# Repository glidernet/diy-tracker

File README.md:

# diy-tracker
Do-it-Yourself OGN Tracker software

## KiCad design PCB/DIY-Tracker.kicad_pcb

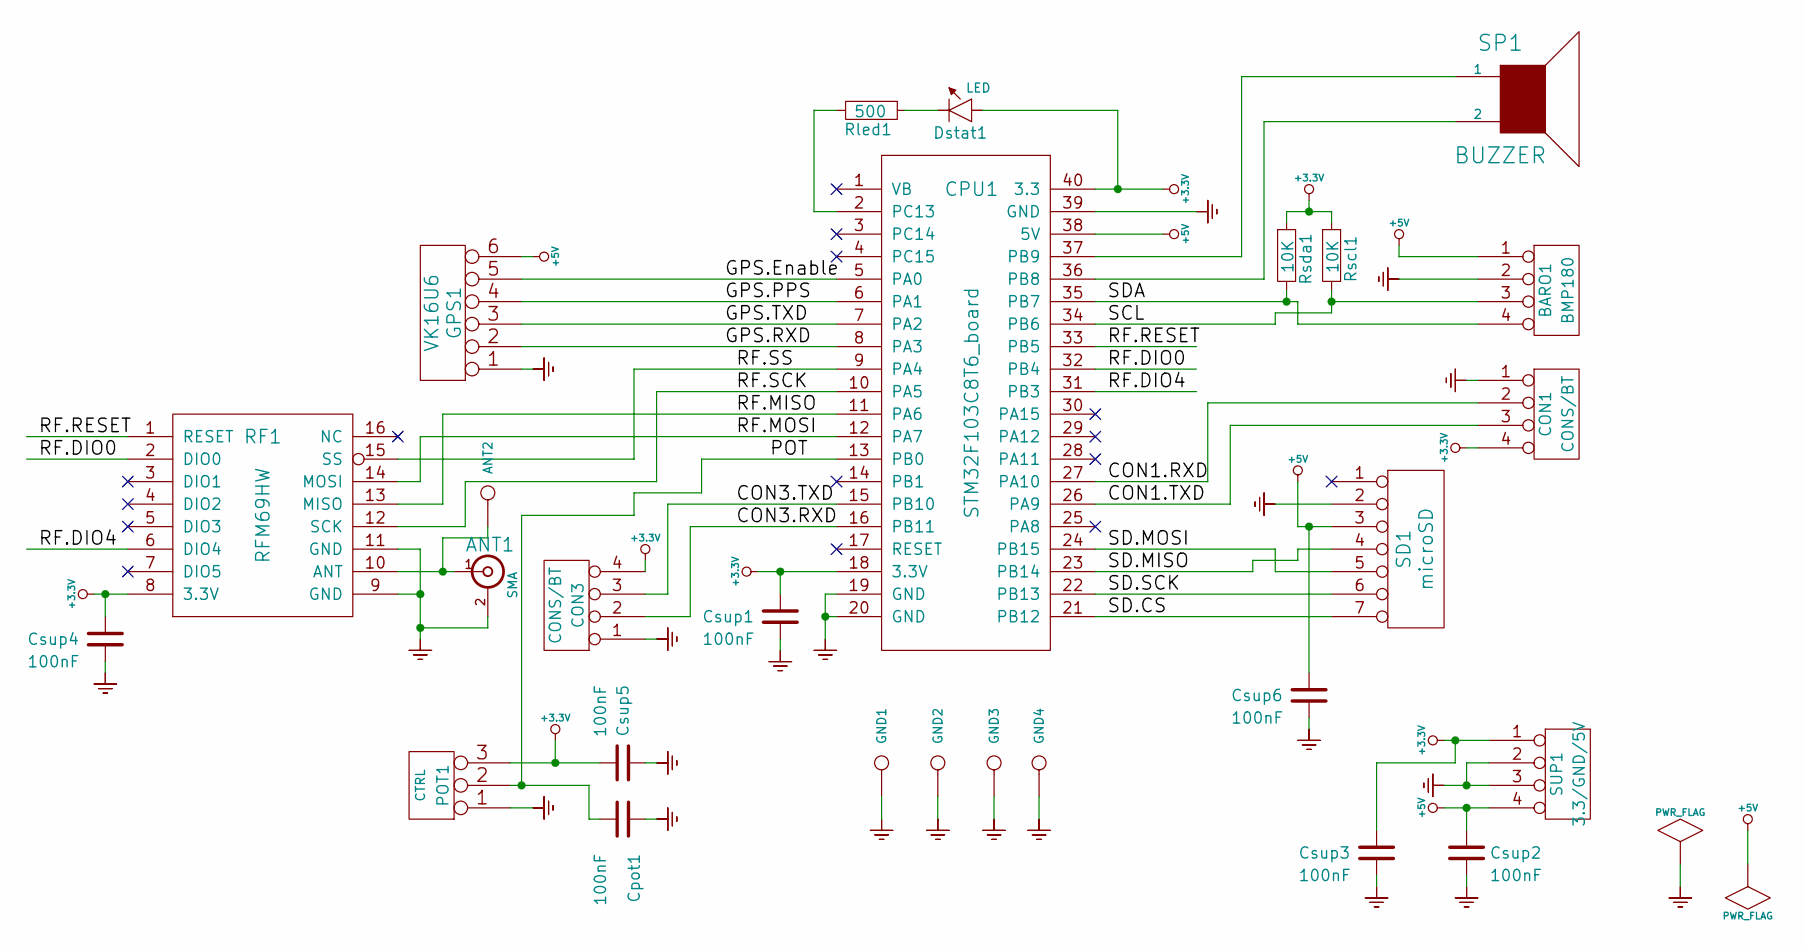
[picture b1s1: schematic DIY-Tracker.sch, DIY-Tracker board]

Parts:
ANT1: SMA; SIL-2
ANT2: CONN_1; 1pin
BARO1: BMP180; SIL-4
CON1, CON3: CONS/BT; SIL-4
CPU1: STM32F103C8T6_board; DIP-40__600_ELL
Cpot1: 100nF; c_1206
Csup1, Csup2, Csup3, Csup4, Csup5, Csup6: 100nF; c_1206
Dstat1: LED; SIL-2
GND1, GND2, GND3, GND4: CONN_1; 1pin
GPS1: VK16U6; SIL-6
POT1: CTRL; SIL-3
RF1: RFM69HW
Rled1: 500; c_1206
Rscl1: 10K; c_1206
Rsda1: 10K; c_1206
SD1: microSD; SIL-7
SP1: BUZZER; SIL-2
SUP1: 3.3/GND/5V; SIL-4

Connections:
+3.3V: CON1.4, CON3.4, CPU1.18 (3.3V), CPU1.40 (3.3), Csup1.1, Csup3.1, Csup4.1, Csup5.2, Dstat1.1 (A), POT1.3, RF1.8 (3.3V), Rscl1.1, Rsda1.1, SUP1.1
+5V: BARO1.1, CPU1.38 (5V), Csup2.1, Csup6.1, GPS1.6, SD1.3, SUP1.4
/CON1.RXD: CON1.2, CPU1.27 (PA10)
/CON1.TXD: CON1.3, CPU1.26 (PA9)
/CON3.RXD: CON3.2, CPU1.16 (PB11)
/CON3.TXD: CON3.3, CPU1.15 (PB10)
/GPS.Enable: CPU1.5 (PA0), GPS1.5
/GPS.PPS: CPU1.6 (PA1), GPS1.4
/GPS.RXD: CPU1.8 (PA3), GPS1.2
/GPS.TXD: CPU1.7 (PA2), GPS1.3
/POT: CPU1.13 (PB0), Cpot1.2, POT1.2 (PM)
/RF.DIO0: CPU1.32 (PB4), RF1.2 (DIO0)
/RF.DIO4: CPU1.31 (PB3), RF1.6 (DIO4)
/RF.MISO: CPU1.11 (PA6), RF1.13 (MISO)
/RF.MOSI: CPU1.12 (PA7), RF1.14 (MOSI)
/RF.RESET: CPU1.33 (PB5), RF1.1 (RESET)
/RF.SCK: CPU1.10 (PA5), RF1.12 (SCK)
/RF.SS: CPU1.9 (PA4), RF1.15 (SS)
/SCL: BARO1.3, CPU1.34 (PB6), Rscl1.2
/SD.CS: CPU1.21 (PB12), SD1.7
/SD.MISO: CPU1.23 (PB14), SD1.4
/SD.MOSI: CPU1.24 (PB15), SD1.5
/SD.SCK: CPU1.22 (PB13), SD1.6
/SDA: BARO1.4, CPU1.35 (PB7), Rsda1.2
GND: ANT1.2 (Ext), BARO1.2, CON1.1, CON3.1, CPU1.19 (GND), CPU1.20 (GND), CPU1.39 (GND), Cpot1.1, Csup1.2, Csup2.2, Csup3.2, Csup4.2, Csup5.1, Csup6.2, GND1.1, GND2.1, GND3.1, GND4.1, GPS1.1, POT1.1, RF1.9 (GND), RF1.11 (GND), SD1.2, SUP1.2, SUP1.3
unnamed: ANT1.1 (In), ANT2.1, RF1.10 (ANT)
unnamed: CPU1.2 (PC13), Rled1.2
unnamed: CPU1.36 (PB8), SP1.2
unnamed: CPU1.37 (PB9), SP1.1
unnamed: Dstat1.2 (K), Rled1.1

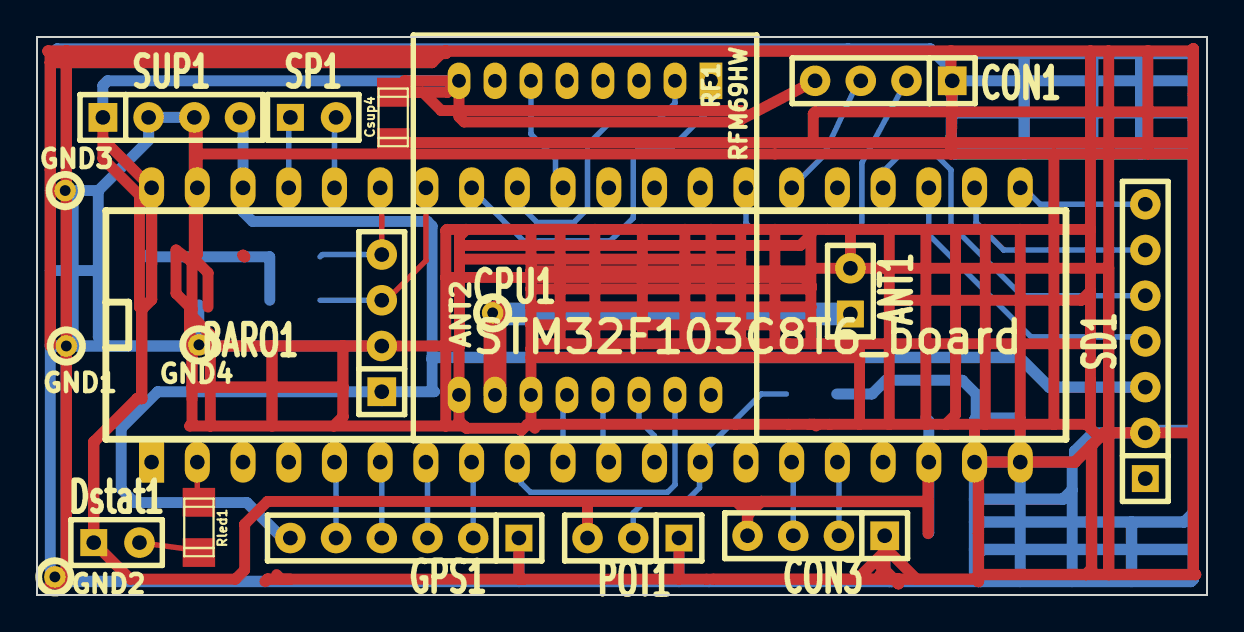
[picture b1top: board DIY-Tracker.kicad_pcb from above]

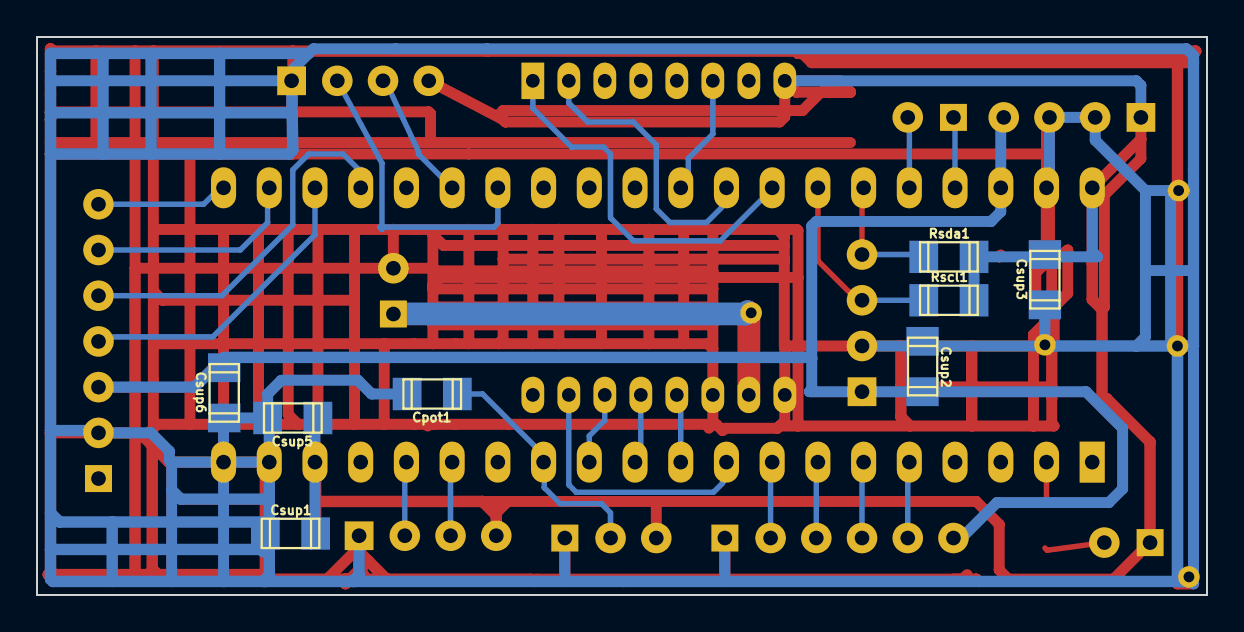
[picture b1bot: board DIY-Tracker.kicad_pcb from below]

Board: 2 copper layers, 65.0 x 31.0 mm, 27 parts (8 on the bottom side), 30 nets.

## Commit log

2015-03-23 Initial upload, transmission timing
2015-03-26 clean console
2015-04-13 Default Tx power (and RF chip type)
2015-06-09 Major code rewrite, BMP180 baro, microSD CARD
2015-06-18 making extra features optional
2015-06-19 making extra features optional; code cleanup
2015-06-21 =Run on internal osc. when no Xtal
2015-06-22 atan2 in intmath.h/cpp
2015-06-22 Potentiometer knob added
2015-06-23 Knob support code
2015-06-23 IntDistance(dX,dY) added
2015-06-23 lcd 5110 introduction
2015-06-23 lcd control with buttons
2015-06-23 refactored io pin configuration
2015-06-23 reversed changes to optional features compilation
2015-06-24 corrected lcd string formatting
2015-06-25 Create LICENSE
    adding license file
2015-06-28 add unions for bytes and words
2015-07-09 instead of digital control buttons use ananlog ladder (saves input pins)
2015-07-09 lcd: showing list of planes around
2015-07-10 lcd: refined pages
2015-07-13 lcd: flipped screen
2015-07-26 lot of small fixes
2015-07-26 clean up
2015-08-07 Packet relay, transmit baro data
2015-08-08 forgot to add format.h
2015-08-08 small bug in PrioQueue and some comments
2015-08-08 packet-relay, tx timing
2015-08-12 BMP180 recovery, SDlog fully buffered by a FIFO, few bugs fixed
2015-08-12 system would dead-lock on writing to log-file buffer: fixed
2015-08-13 some comments, small improvements
2015-08-13 Bug fixed around copying time from one GPS record to the next
2015-08-14 Did not compile without BMP180, small omission fixed
2015-08-15 Tracker would transmit zero-coordinate when GPS lock was lost - fixed
2015-08-20 More compile options, not all in full use yet
2015-09-08 Add PCB files: KiCAD project
2015-11-09 Support for GNxxx NMEA sentences (GLONASS and GLONASS+GPS) - not tested
2016-01-12 Organize RF in channels
2016-08-22 Bug fix in Unix time calculation
2017-03-16 Major rewrite, several bugs fixed, frequency plan for other continents
2017-04-21 Various improvements and options
2017-04-21 Limit bandwidth of some I/O pins to reduce noise
2017-04-21 Fixed conflict between knob and OGN-CURE-1 RF
2017-04-24 Now works with OGN-CUBE-1
2017-04-24 BMP280 support, yet incomplete
2017-04-25 support not complete yet
2017-04-25 BMP280 support, but not complete yet
2017-04-25 Bug fixed in pressure altitude encoding
2017-04-25 BMP280 support, to be tested
2017-04-25 Autobaud on GPS UART, not tested
2017-04-25 Minor corrections
2017-04-29 Fix RFM95 transmission
2017-05-01 BMP280 is now working on OGN-CUBE-1
2017-05-02 Double the BMP280 sampling for lower noise
2017-05-02 Pass-through for GPS control frames from/to the console
2017-05-08 Tracker status packets implemented
2017-05-16 Fixed compile with no baro chip
2017-05-16 Delay after STANDBY request before changing the frequency.
2017-05-16 Fixed bug in the freq. hopping
2017-05-16 A bit more extensive dump of numbers
2017-08-06 Minor edits
2017-09-30 Support old MMC and SDC1 cards
    These cards do not support CMD8 command and return response 0x05
    instead. According to http://elm-chan.org/docs/mmc/mmc_e.html:
    > If the CMD8 is rejected with illigal command error (0x05), the card is
    > SDC version 1 or MMC version 3.
    This adds support for such cards.
2017-10-01 Hardware Abstraction Layer (not all peryferials included yet) for easier porting
2017-10-04 Set GPS to higher baud rate and to airborne dynamic mode
2017-10-04 Fixed baro measurement taking too long with the high baud rate on the GPS
2017-10-07 Old bug in pressure altitude calculation was back - fixed again
2017-11-22 Add initial support for SX1272 radio chip
2017-11-22 Minor cleanups
2018-01-13 Correct checksum loop
    Not sure why this works with `-Os` optimizations, but without compiler
    optimizations (`-O0`) MCU goes into (almost) infinite loop.
2018-01-13 Silence beeper on startup
2018-01-13 Wait longer for valid GPS signal before switching baud rate
    Otherwise GPS tunes out from a good baud rate from time to time.
2018-02-25 FlashLog, Push I2C to HAL, essential files are identical now to the ESP32 version for easy passing of new features
2018-02-26 Minor fixes
2018-02-26 Fix compilation issues if WITH_SDLOG is defined
2018-02-26 Support compiling with UBX support for GPS configuration
2018-02-28 Add BME280 support, by Ronald
2018-02-28 Bring back standard compiler path and the compile options
2018-03-05 Only append \n to NMEA checksum
    We will convert \n to a proper \r\n sequence in `Format_String`
    (and friends) before outputing it to serial console.
    Without this, we are outputing strings with too many `\r` characters -
    `\r\n` is converted to `\r\r\n` by `Format_String`. This makes output
    unparseable by XCSoar.
2018-03-05 Fix compilation issue with MAPLE_MINI
2018-03-05 Add missing PFLAA compilation option
2018-03-08 Update bme280.h
    fixed an over loading mistake in Acquire() .
2018-03-09 Add some info-parameters, move I2C mutex into hal.cpp
2018-07-23 Add support for 433MHz band and parameter to force given frequency plan
2018-11-08 new encoding for temperature and humidity to increase accuracy around the normal values
